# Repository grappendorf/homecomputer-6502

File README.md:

HomeComputer 6502
=================

This is my attempt to build a simple, mobile microcomputer system with an 8-bit MOS 6502 CPU that was used in many popular
home computers of the 1970s and 1980s like the Commodore 64 or the Apple II.

The idea was to design a computer like the C64, almost only using parts that were available when this computer was
manufactured.

The hardware is designed with [Eagle](http://www.cadsoft.de/eagle-pcb-design-software/).

The software is written in 6502 assembler and C, with the help of the [CC65 compiler/assembler](http://cc65.github.io/cc65/).

The case is designed with [Autodesk 123D Design](http://www.123dapp.com/design).

Documentation of this project can be found on my website: http://www.grappendorf.net/projects/6502-home-computer

This repositiory contains the following files:

* eagle - Eagle schematic and board files
* schematics - PDF schematics
* case - 123D/STL design files for the case
* firmware - Minimal BASIC interpreter written with CC65,  different versions of the firmware during the development process
* terminal -  Small ruby script for loading/saving of BASIC programs, example BASIC programs

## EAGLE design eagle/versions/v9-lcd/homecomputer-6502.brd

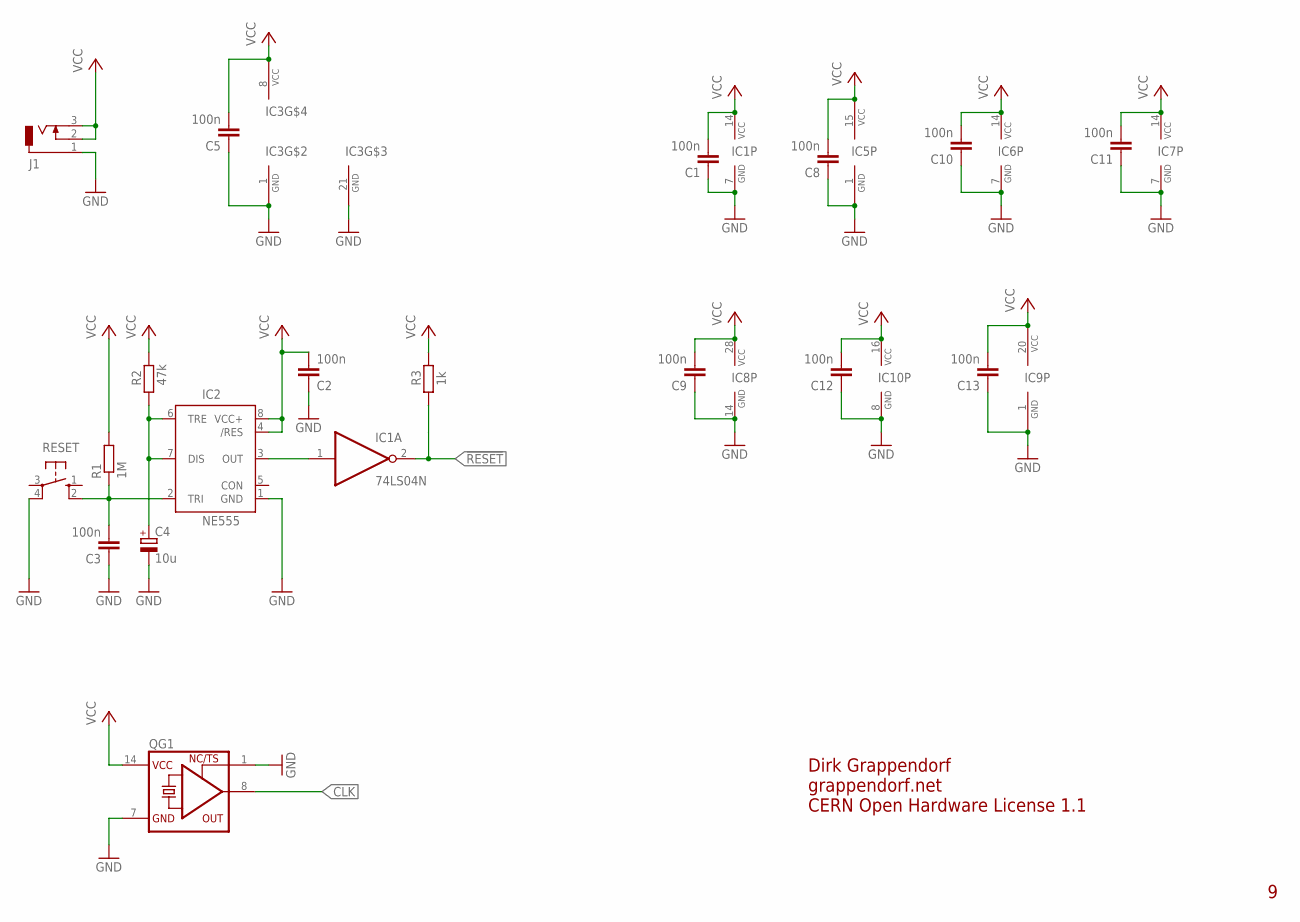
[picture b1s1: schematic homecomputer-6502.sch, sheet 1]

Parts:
C1, C2, C3, C5, C8, C9, C10, C11, C12, C13: 100n; C025-024X044
C4: 10u; E2,5-6E
IC1: 74LS04N; DIL14
IC2: NE555; DIL-08
IC3: 6502; DIP40
IC5: 6551; DIP28
IC6: 74LS00N; DIL14
IC7: 74LS30N; DIL14
IC8: 61256; DIL28-3
IC9: 6522; DIP40
IC10: 74LS137N; DIL16
J1: DCJ0303
QG1: XO-14; DIL14S
R1: 1M; 0204/5
R2: 47k; 0204/5
R3: 1k; 0204/5
RESET: 10-XX; B3F-10XX

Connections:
!RESET: IC1.2 (O), R3.1; also elsewhere on the board
CLK: QG1.8 (OUT); also elsewhere on the board
GND: C1.1, C2.1, C3.1, C4.-, C5.1, C8.1, C9.1, C10.1, C11.1, C12.1, C13.1, IC1.7 (GND), IC2.1 (GND), IC3.1 (GND), IC3.21 (GND), IC5.1 (GND), IC6.7 (GND), IC7.7 (GND), IC8.14 (GND), IC9.1 (GND), IC10.8 (GND), J1.1, QG1.1 (TS), QG1.7 (GND), RESET.4 (P1); also elsewhere on the board
unnamed: C4.+, IC2.6 (TRE), IC2.7 (DIS), R2.1
unnamed: IC1.1 (I), IC2.3 (OUT)
unnamed: C3.2, IC2.2 (TRI), R1.1, RESET.2 (S1)
VCC: C1.2, C2.2, C5.2, C8.2, C9.2, C10.2, C11.2, C12.2, C13.2, IC1.14 (VCC), IC2.4 (/RES), IC2.8 (VCC+), IC3.8 (VCC), IC5.15 (VCC), IC6.14 (VCC), IC7.14 (VCC), IC8.28 (VCC), IC9.20 (VCC), IC10.16 (VCC), J1.2, J1.3, QG1.14 (VCC), R1.2, R2.2, R3.2; also elsewhere on the board

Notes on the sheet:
Dirk Grappendorf
grappendorf.net
CERN Open Hardware License 1.1

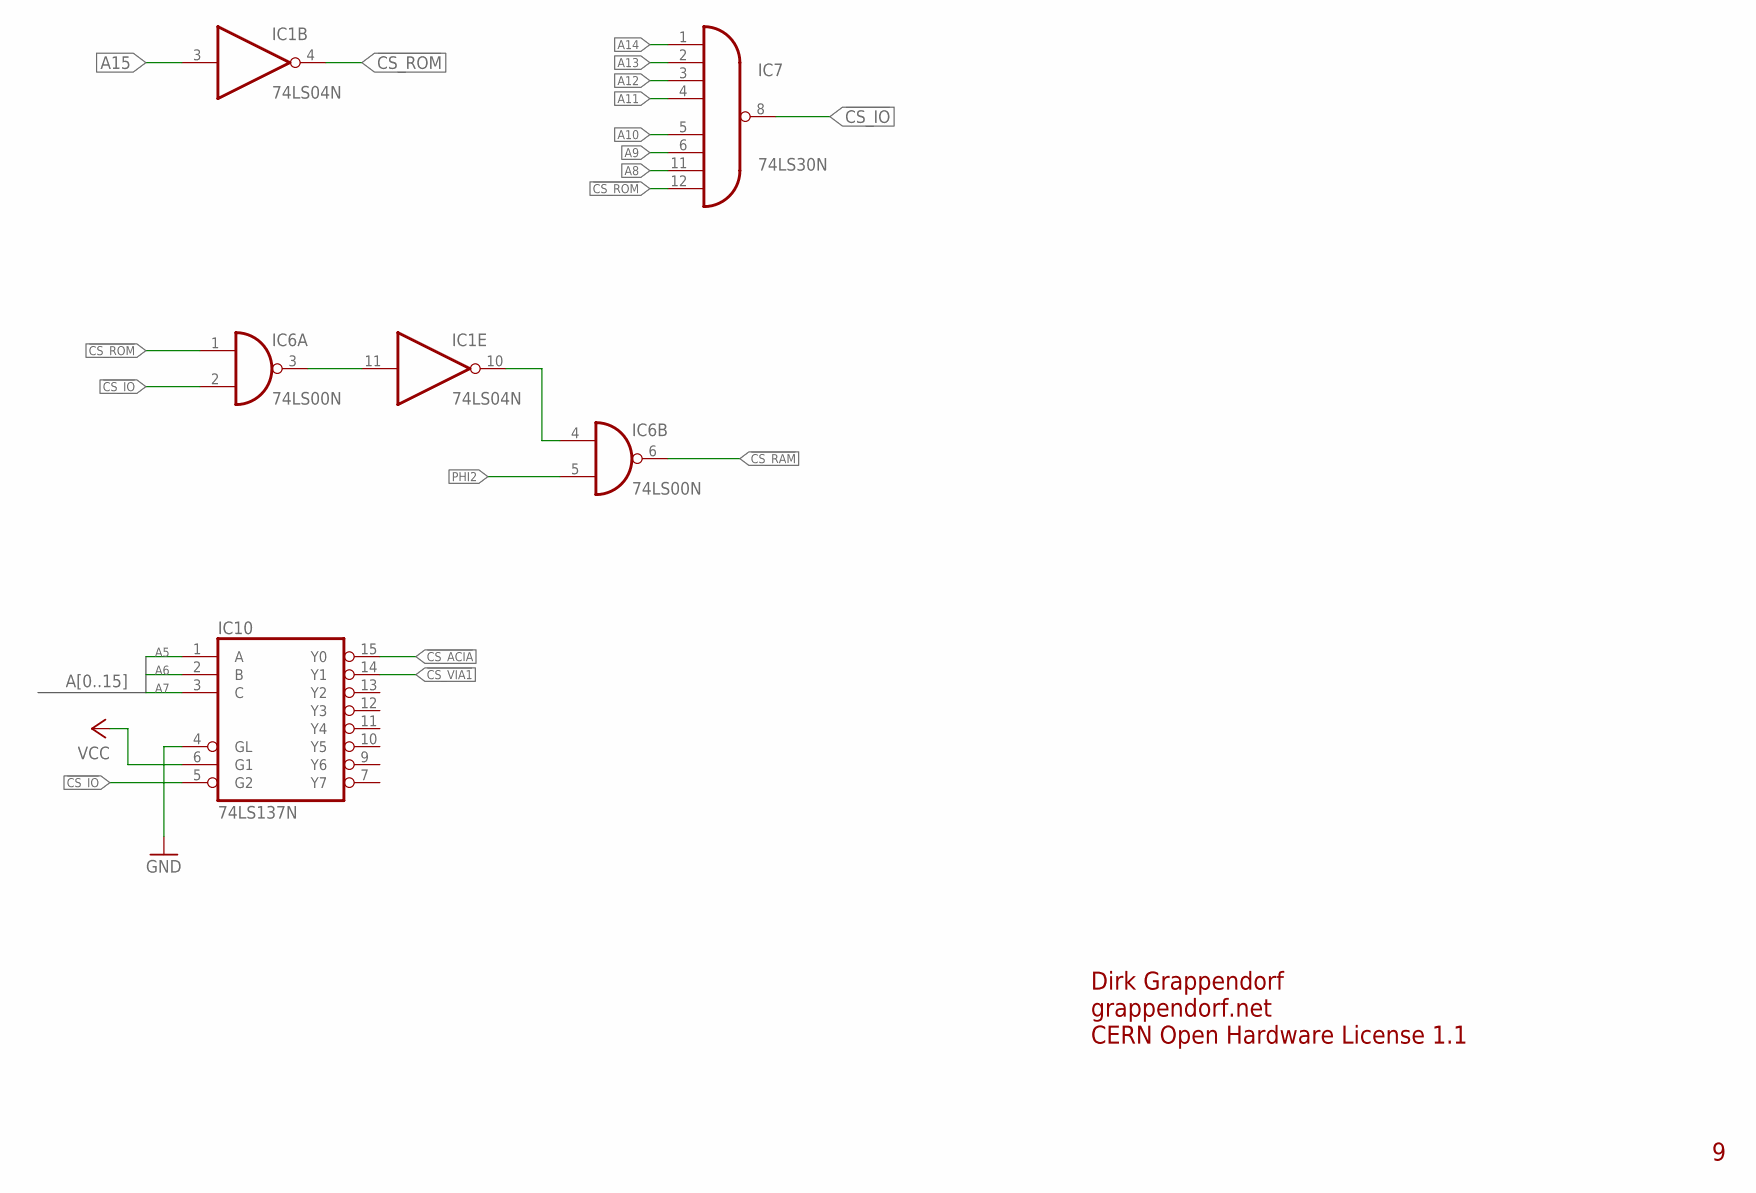
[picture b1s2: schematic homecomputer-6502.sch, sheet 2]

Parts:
IC1: 74LS04N; DIL14
IC6: 74LS00N; DIL14
IC7: 74LS30N; DIL14
IC10: 74LS137N; DIL16

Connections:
!CS_ACIA: IC10.15 (Y0); also elsewhere on the board
!CS_IO: IC6.2 (I1), IC7.8 (O), IC10.5 (G2)
!CS_RAM: IC6.6 (O); also elsewhere on the board
!CS_ROM: IC1.4 (O), IC6.1 (I0), IC7.12 (I7); also elsewhere on the board
!CS_VIA1: IC10.14 (Y1); also elsewhere on the board
A5: IC10.1 (A); also elsewhere on the board
A6: IC10.2 (B); also elsewhere on the board
A7: IC10.3 (C); also elsewhere on the board
A8: IC7.11 (I6); also elsewhere on the board
A9: IC7.6 (I5); also elsewhere on the board
A10: IC7.5 (I4); also elsewhere on the board
A11: IC7.4 (I3); also elsewhere on the board
A12: IC7.3 (I2); also elsewhere on the board
A13: IC7.2 (I1); also elsewhere on the board
A14: IC7.1 (I0); also elsewhere on the board
A15: IC1.3 (I); also elsewhere on the board
GND: IC10.4 (GL); also elsewhere on the board
unnamed: IC1.11 (I), IC6.3 (O)
unnamed: IC1.10 (O), IC6.4 (I0)
PHI2: IC6.5 (I1); also elsewhere on the board
VCC: IC10.6 (G1); also elsewhere on the board

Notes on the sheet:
Dirk Grappendorf
grappendorf.net
CERN Open Hardware License 1.1

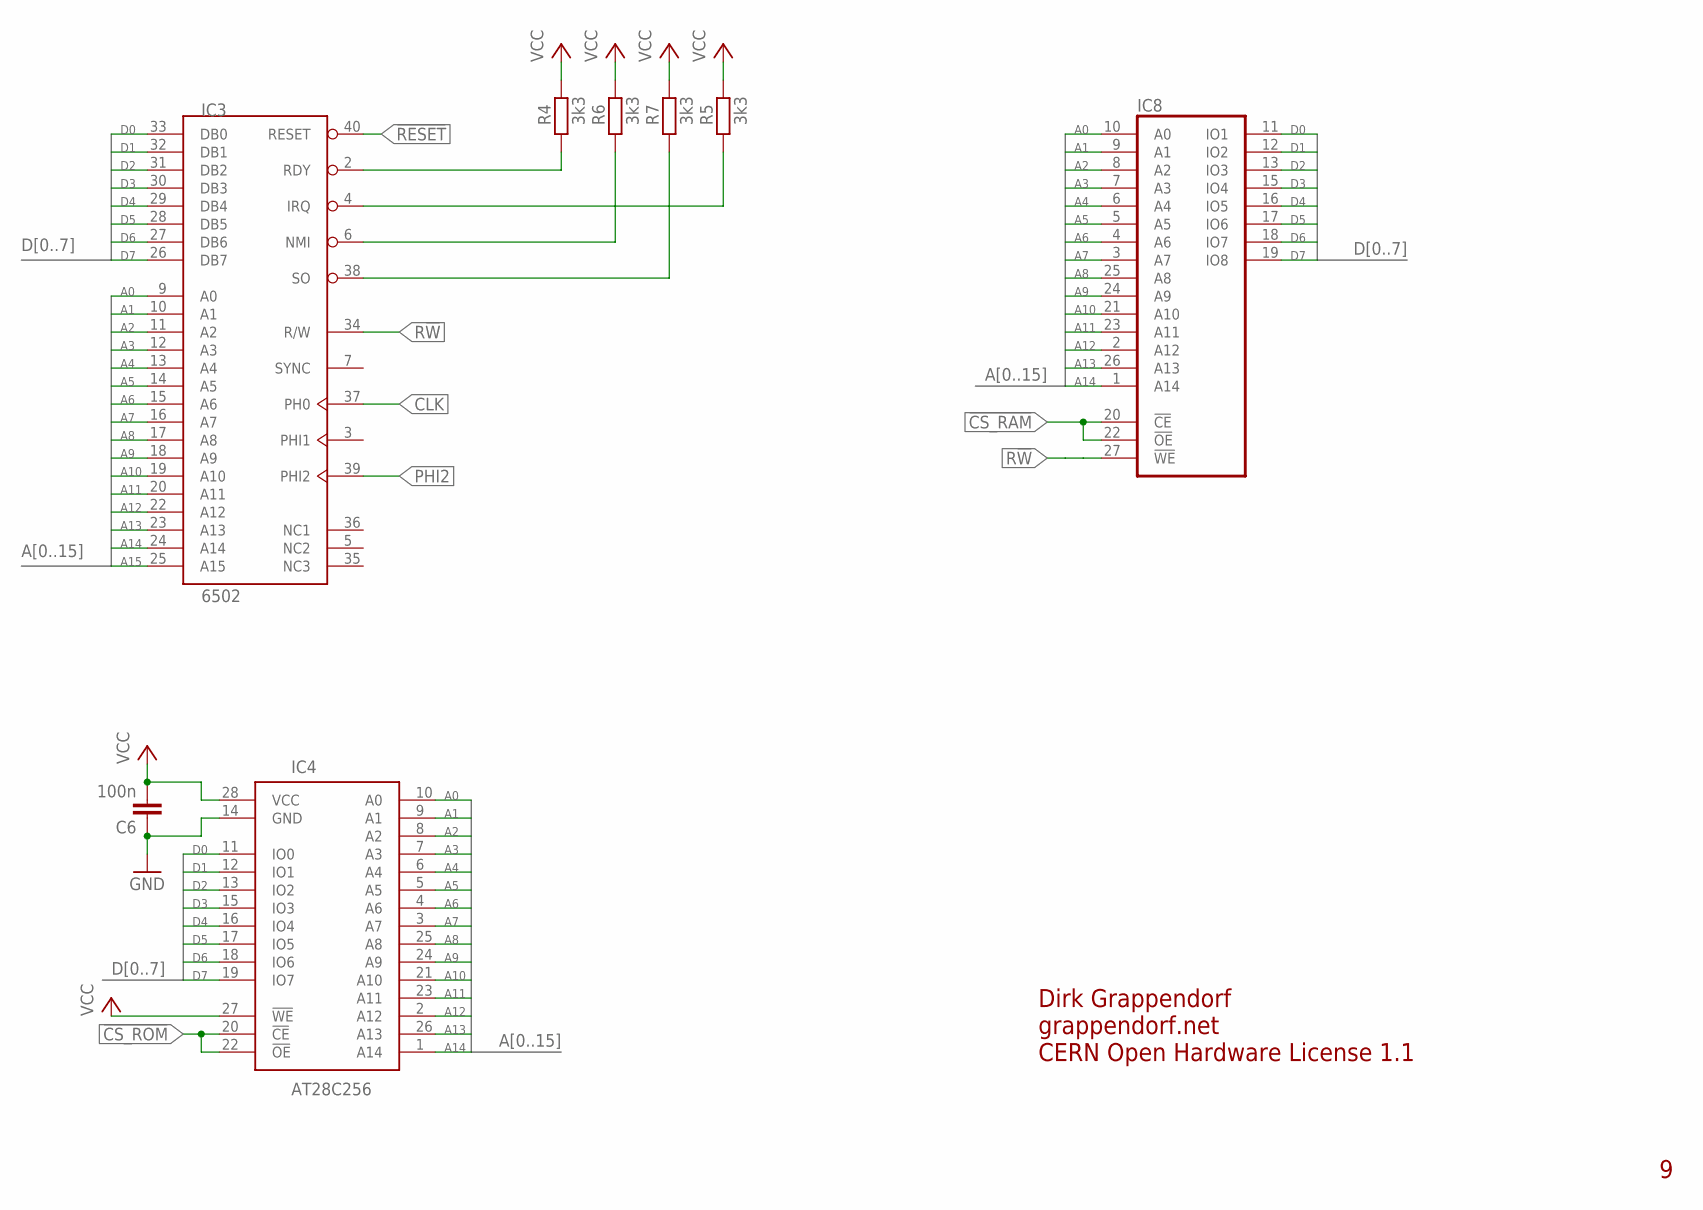
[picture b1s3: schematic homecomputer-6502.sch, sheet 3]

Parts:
C6: 100n; C025-024X044
IC3: 6502; DIP40
IC4: AT28C256; DIL28-6
IC8: 61256; DIL28-3
R4, R5, R6, R7: 3k3; 0204/5

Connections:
!CS_RAM: IC8.20 (!CE), IC8.22 (!OE); also elsewhere on the board
!CS_ROM: IC4.20 (!CE), IC4.22 (!OE); also elsewhere on the board
!IRQ: IC3.4 (IRQ), R5.1
!RESET: IC3.40 (RESET); also elsewhere on the board
A0: IC3.9 (A0), IC4.10 (A0), IC8.10 (A0); also elsewhere on the board
A1: IC3.10 (A1), IC4.9 (A1), IC8.9 (A1); also elsewhere on the board
A2: IC3.11 (A2), IC4.8 (A2), IC8.8 (A2); also elsewhere on the board
A3: IC3.12 (A3), IC4.7 (A3), IC8.7 (A3); also elsewhere on the board
A4: IC3.13 (A4), IC4.6 (A4), IC8.6 (A4)
A5: IC3.14 (A5), IC4.5 (A5), IC8.5 (A5); also elsewhere on the board
A6: IC3.15 (A6), IC4.4 (A6), IC8.4 (A6); also elsewhere on the board
A7: IC3.16 (A7), IC4.3 (A7), IC8.3 (A7); also elsewhere on the board
A8: IC3.17 (A8), IC4.25 (A8), IC8.25 (A8); also elsewhere on the board
A9: IC3.18 (A9), IC4.24 (A9), IC8.24 (A9); also elsewhere on the board
A10: IC3.19 (A10), IC4.21 (A10), IC8.21 (A10); also elsewhere on the board
A11: IC3.20 (A11), IC4.23 (A11), IC8.23 (A11); also elsewhere on the board
A12: IC3.22 (A12), IC4.2 (A12), IC8.2 (A12); also elsewhere on the board
A13: IC3.23 (A13), IC4.26 (A13), IC8.26 (A13); also elsewhere on the board
A14: IC3.24 (A14), IC4.1 (A14), IC8.1 (A14); also elsewhere on the board
A15: IC3.25 (A15); also elsewhere on the board
CLK: IC3.37 (PH0); also elsewhere on the board
D0: IC3.33 (DB0), IC4.11 (IO0), IC8.11 (IO1); also elsewhere on the board
D1: IC3.32 (DB1), IC4.12 (IO1), IC8.12 (IO2); also elsewhere on the board
D2: IC3.31 (DB2), IC4.13 (IO2), IC8.13 (IO3); also elsewhere on the board
D3: IC3.30 (DB3), IC4.15 (IO3), IC8.15 (IO4); also elsewhere on the board
D4: IC3.29 (DB4), IC4.16 (IO4), IC8.16 (IO5); also elsewhere on the board
D5: IC3.28 (DB5), IC4.17 (IO5), IC8.17 (IO6); also elsewhere on the board
D6: IC3.27 (DB6), IC4.18 (IO6), IC8.18 (IO7); also elsewhere on the board
D7: IC3.26 (DB7), IC4.19 (IO7), IC8.19 (IO8); also elsewhere on the board
GND: C6.1, IC4.14 (GND); also elsewhere on the board
unnamed: IC3.2 (RDY), R4.1
unnamed: IC3.6 (NMI), R6.1
unnamed: IC3.38 (SO), R7.1
PHI2: IC3.39 (PHI2); also elsewhere on the board
R!W: IC3.34 (R/W), IC8.27 (!WE); also elsewhere on the board
VCC: C6.2, IC4.27 (!WE), IC4.28 (VCC), R4.2, R5.2, R6.2, R7.2; also elsewhere on the board

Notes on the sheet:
Dirk Grappendorf
grappendorf.net
CERN Open Hardware License 1.1

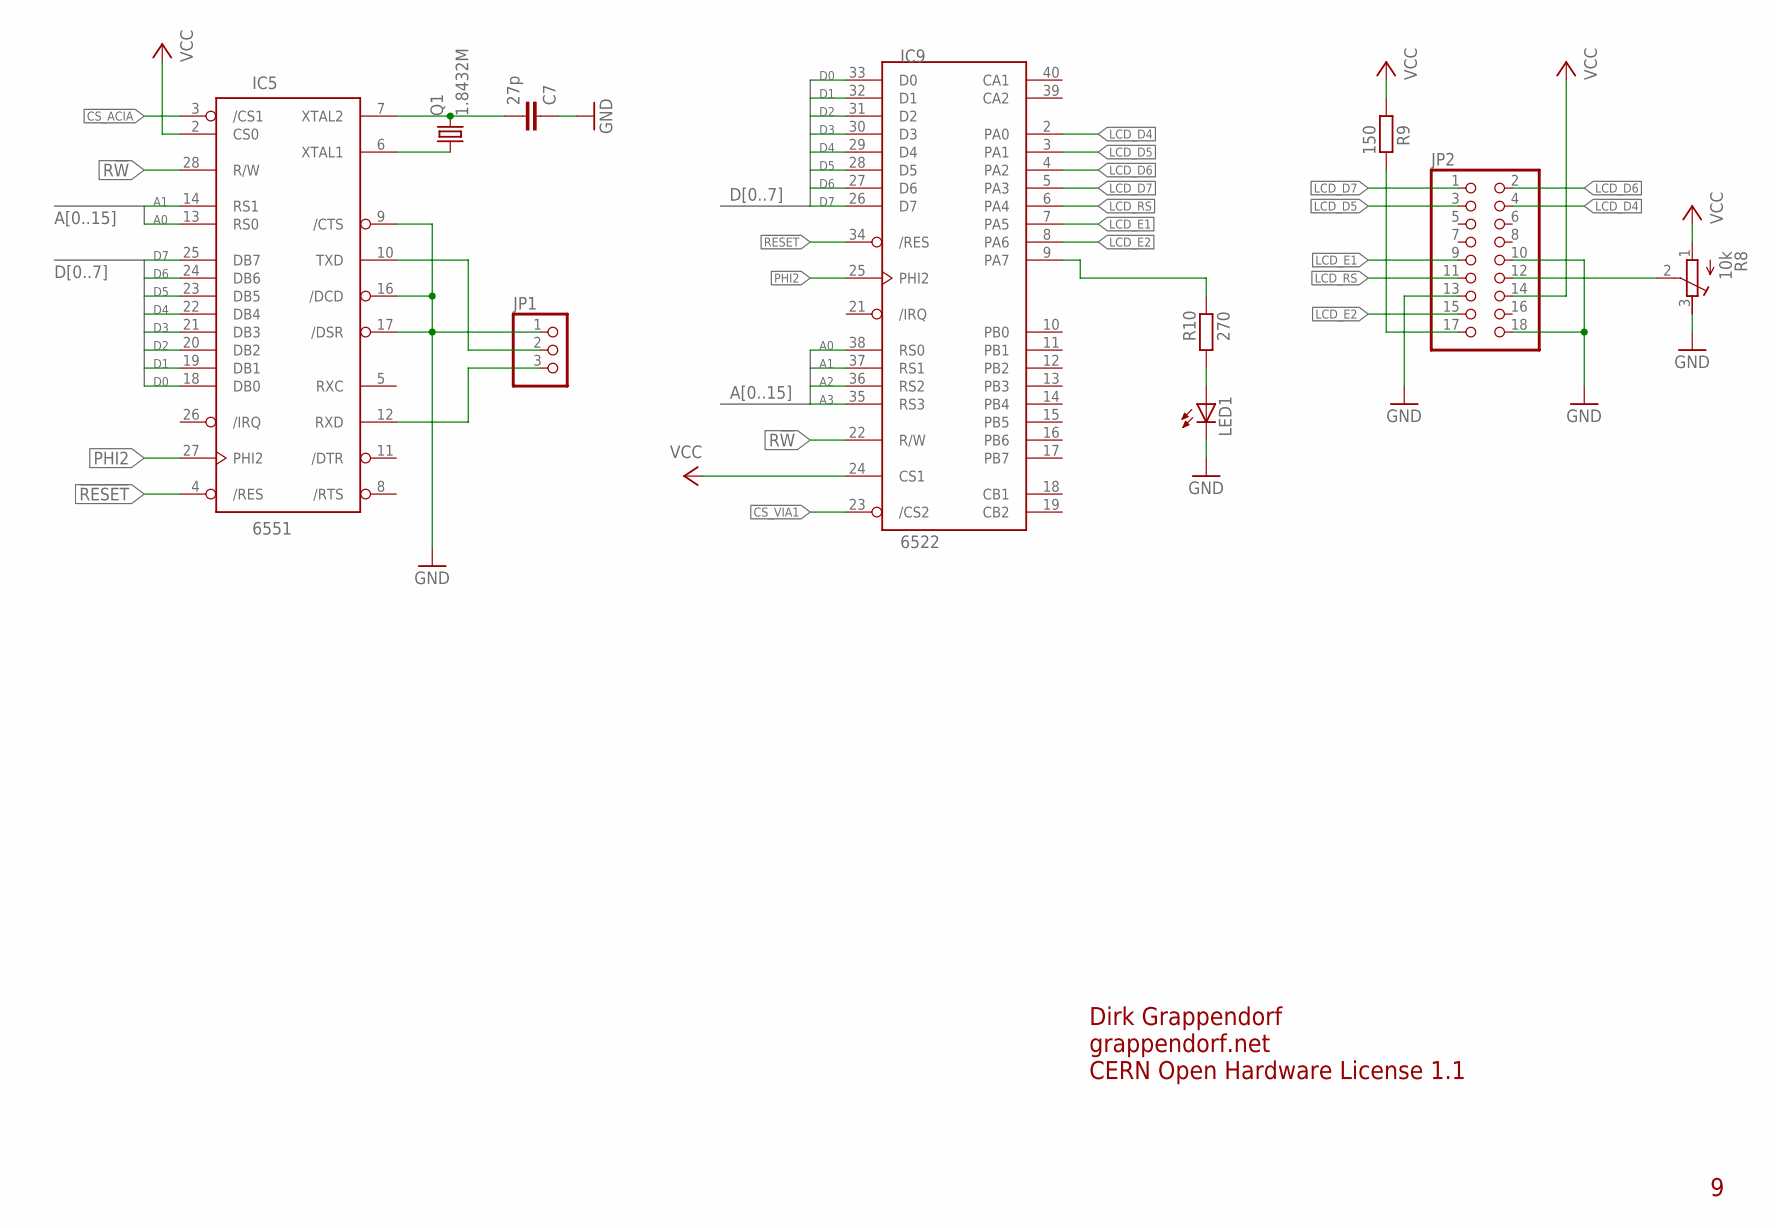
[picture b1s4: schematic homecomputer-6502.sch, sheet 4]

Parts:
C7: 27p; C025-024X044
IC5: 6551; DIP28
IC9: 6522; DIP40
JP1: PINHD-1X3_2.54; 1X03
JP2: PINHD-2X9_2.54; 2X09
LED1: LED3MM
Q1: 1.8432M; HC49U-V
R8: 10k; RTRIM3339P
R9: 150; 0204/5
R10: 270; 0204/5

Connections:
!CS_ACIA: IC5.3 (/CS1); also elsewhere on the board
!CS_VIA1: IC9.23 (/CS2); also elsewhere on the board
!RESET: IC5.4 (/RES), IC9.34 (/RES); also elsewhere on the board
A0: IC5.13 (RS0), IC9.38 (RS0); also elsewhere on the board
A1: IC5.14 (RS1), IC9.37 (RS1); also elsewhere on the board
A2: IC9.36 (RS2); also elsewhere on the board
A3: IC9.35 (RS3); also elsewhere on the board
D0: IC5.18 (DB0), IC9.33 (D0); also elsewhere on the board
D1: IC5.19 (DB1), IC9.32 (D1); also elsewhere on the board
D2: IC5.20 (DB2), IC9.31 (D2); also elsewhere on the board
D3: IC5.21 (DB3), IC9.30 (D3); also elsewhere on the board
D4: IC5.22 (DB4), IC9.29 (D4); also elsewhere on the board
D5: IC5.23 (DB5), IC9.28 (D5); also elsewhere on the board
D6: IC5.24 (DB6), IC9.27 (D6); also elsewhere on the board
D7: IC5.25 (DB7), IC9.26 (D7); also elsewhere on the board
GND: C7.1, IC5.9 (/CTS), IC5.16 (/DCD), IC5.17 (/DSR), JP1.1, JP2.10, JP2.13, JP2.18, LED1.K (C), R8.3 (E); also elsewhere on the board
LCD_D4: IC9.2 (PA0), JP2.4
LCD_D5: IC9.3 (PA1), JP2.3
LCD_D6: IC9.4 (PA2), JP2.2
LCD_D7: IC9.5 (PA3), JP2.1
LCD_E1: IC9.7 (PA5), JP2.9
LCD_E2: IC9.8 (PA6), JP2.15
LCD_RS: IC9.6 (PA4), JP2.11
unnamed: C7.2, IC5.7 (XTAL2), Q1.2
unnamed: IC5.6 (XTAL1), Q1.1
unnamed: IC5.10 (TXD), JP1.2
unnamed: IC9.9 (PA7), R10.2
unnamed: IC5.12 (RXD), JP1.3
unnamed: JP2.12, R8.2 (S)
unnamed: JP2.17, R9.2
unnamed: LED1.A, R10.1
PHI2: IC5.27 (PHI2), IC9.25 (PHI2); also elsewhere on the board
R!W: IC5.28 (R/W), IC9.22 (R/W); also elsewhere on the board
VCC: IC5.2 (CS0), IC9.24 (CS1), JP2.14, R8.1 (A), R9.1; also elsewhere on the board

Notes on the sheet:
Dirk Grappendorf
grappendorf.net
CERN Open Hardware License 1.1

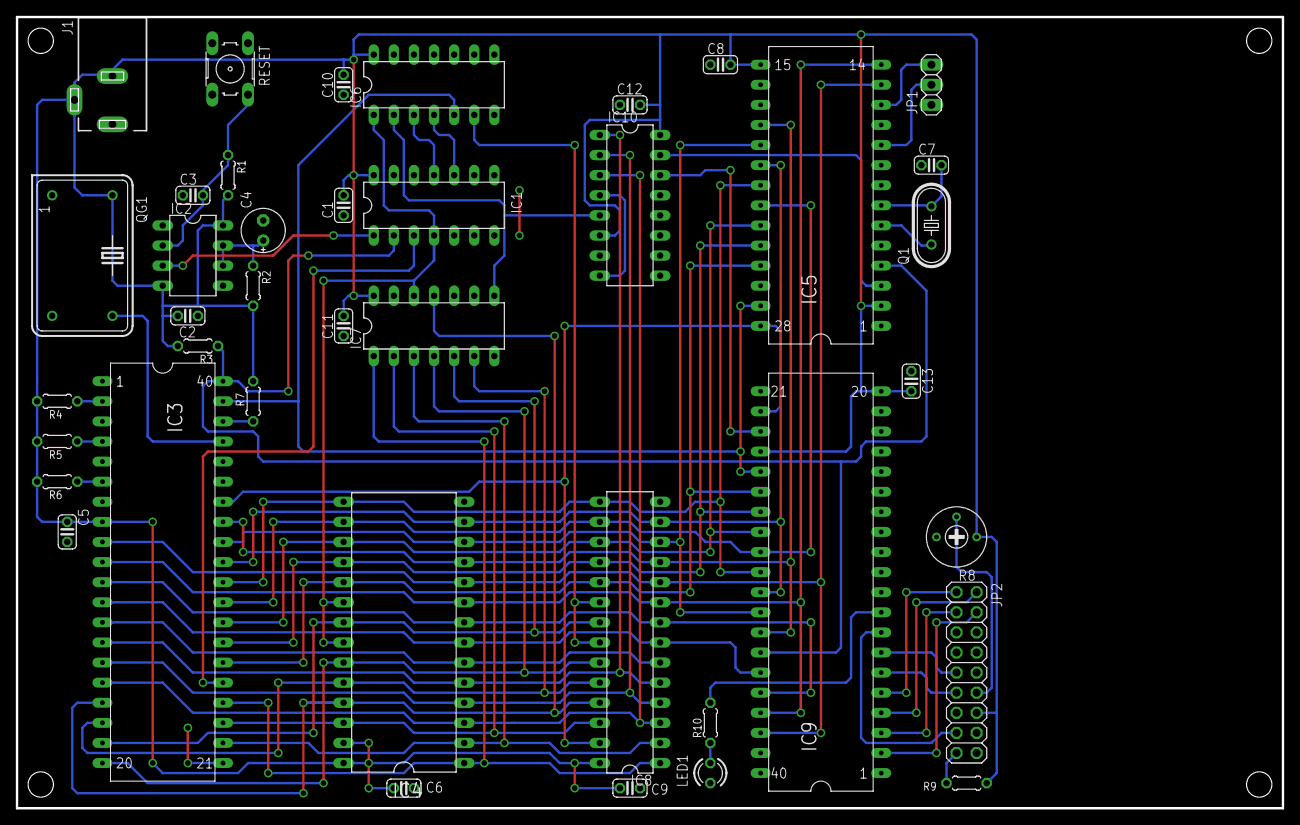
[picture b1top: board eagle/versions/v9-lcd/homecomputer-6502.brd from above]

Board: 3 copper layers, 160.0 x 100.0 mm, 40 parts (0 on the bottom side), 59 nets.

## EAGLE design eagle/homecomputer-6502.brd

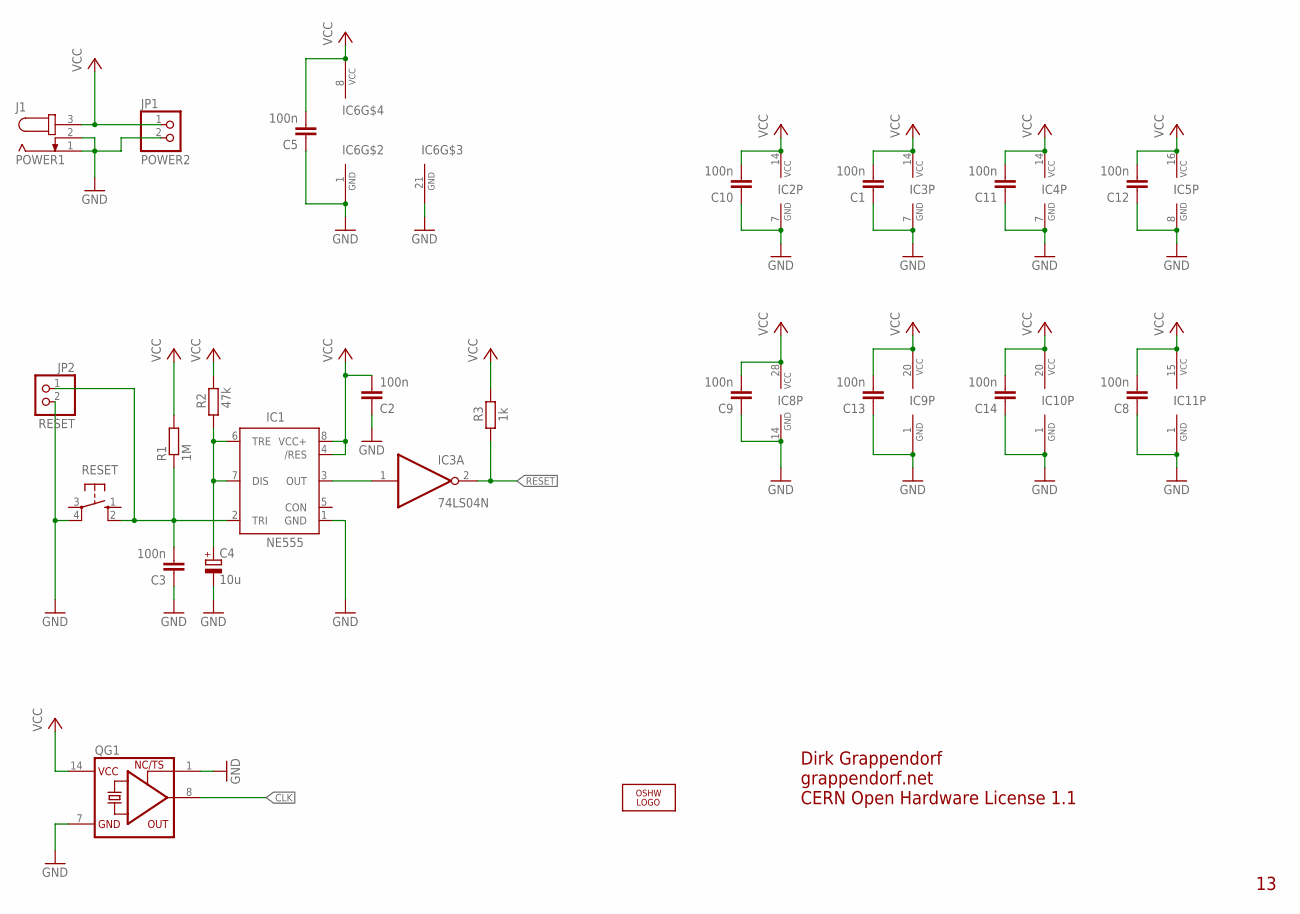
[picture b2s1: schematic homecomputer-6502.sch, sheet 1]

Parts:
C1, C2, C3, C5, C8, C9, C10, C11, C12, C13, C14: 100n; C025-024X044
C4: 10u; E2,5-6E
IC1: NE555; DIL-08
IC2: 74LS00N; DIL14
IC3: 74LS04N; DIL14
IC4: 74LS30N; DIL14
IC5: 74LS137N; DIL16
IC6: 6502; DIP40
IC8: 61256; DIL28-3
IC9, IC10: 6522; DIP40
IC11: 6551; DIP28
J1: POWER1; SPC4078
JP1: POWER2; 1X02
JP2: RESET; 1X02
LOGO1: OSHW_LOGO_8MILX0350-NT; OSHW_8X350_NOTEXT
QG1: XO-14; DIL14S
R1: 1M; 0204/7
R2: 47k; 0204/7
R3: 1k; 0204/7
RESET: 10-XX; B3F-10XX

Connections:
!RESET: IC3.2 (O), R3.1; also elsewhere on the board
CLK: QG1.8 (OUT); also elsewhere on the board
GND: C1.1, C2.1, C3.1, C4.-, C5.1, C8.1, C9.1, C10.1, C11.1, C12.1, C13.1, C14.1, IC1.1 (GND), IC2.7 (GND), IC3.7 (GND), IC4.7 (GND), IC5.8 (GND), IC6.1 (GND), IC6.21 (GND), IC8.14 (GND), IC9.1 (GND), IC10.1 (GND), IC11.1 (GND), J1.1, J1.2, JP1.2, JP2.2, QG1.1 (TS), QG1.7 (GND), RESET.4 (P1); also elsewhere on the board
unnamed: C4.+, IC1.6 (TRE), IC1.7 (DIS), R2.1
unnamed: IC1.3 (OUT), IC3.1 (I)
unnamed: C3.2, IC1.2 (TRI), JP2.1, R1.1, RESET.2 (S1)
VCC: C1.2, C2.2, C5.2, C8.2, C9.2, C10.2, C11.2, C12.2, C13.2, C14.2, IC1.4 (/RES), IC1.8 (VCC+), IC2.14 (VCC), IC3.14 (VCC), IC4.14 (VCC), IC5.16 (VCC), IC6.8 (VCC), IC8.28 (VCC), IC9.20 (VCC), IC10.20 (VCC), IC11.15 (VCC), J1.3, JP1.1, QG1.14 (VCC), R1.2, R2.2, R3.2; also elsewhere on the board

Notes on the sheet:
Dirk Grappendorf
grappendorf.net
CERN Open Hardware License 1.1

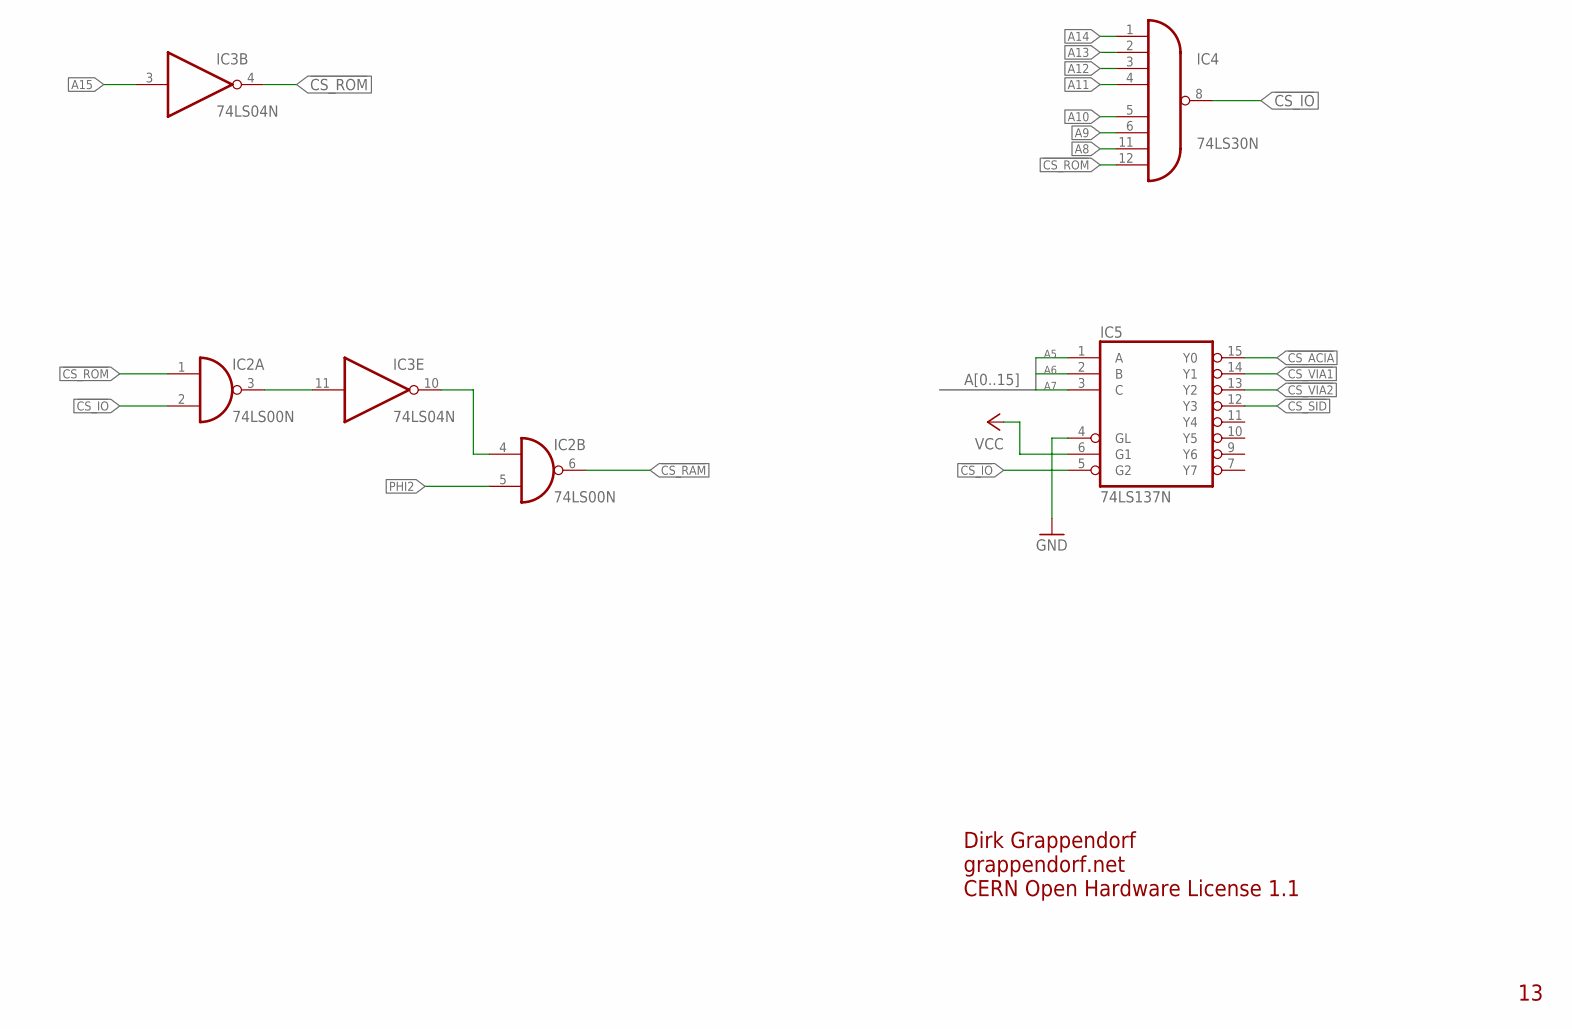
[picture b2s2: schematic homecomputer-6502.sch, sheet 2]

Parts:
IC2: 74LS00N; DIL14
IC3: 74LS04N; DIL14
IC4: 74LS30N; DIL14
IC5: 74LS137N; DIL16

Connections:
!CS_ACIA: IC5.15 (Y0); also elsewhere on the board
!CS_IO: IC2.2 (I1), IC4.8 (O), IC5.5 (G2)
!CS_RAM: IC2.6 (O); also elsewhere on the board
!CS_ROM: IC2.1 (I0), IC3.4 (O), IC4.12 (I7); also elsewhere on the board
!CS_SID: IC5.12 (Y3); also elsewhere on the board
!CS_VIA1: IC5.14 (Y1); also elsewhere on the board
!CS_VIA2: IC5.13 (Y2); also elsewhere on the board
A5: IC5.1 (A); also elsewhere on the board
A6: IC5.2 (B); also elsewhere on the board
A7: IC5.3 (C); also elsewhere on the board
A8: IC4.11 (I6); also elsewhere on the board
A9: IC4.6 (I5); also elsewhere on the board
A10: IC4.5 (I4); also elsewhere on the board
A11: IC4.4 (I3); also elsewhere on the board
A12: IC4.3 (I2); also elsewhere on the board
A13: IC4.2 (I1); also elsewhere on the board
A14: IC4.1 (I0); also elsewhere on the board
A15: IC3.3 (I); also elsewhere on the board
GND: IC5.4 (GL); also elsewhere on the board
unnamed: IC2.3 (O), IC3.11 (I)
unnamed: IC2.4 (I0), IC3.10 (O)
PHI2: IC2.5 (I1); also elsewhere on the board
VCC: IC5.6 (G1); also elsewhere on the board

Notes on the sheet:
Dirk Grappendorf
grappendorf.net
CERN Open Hardware License 1.1

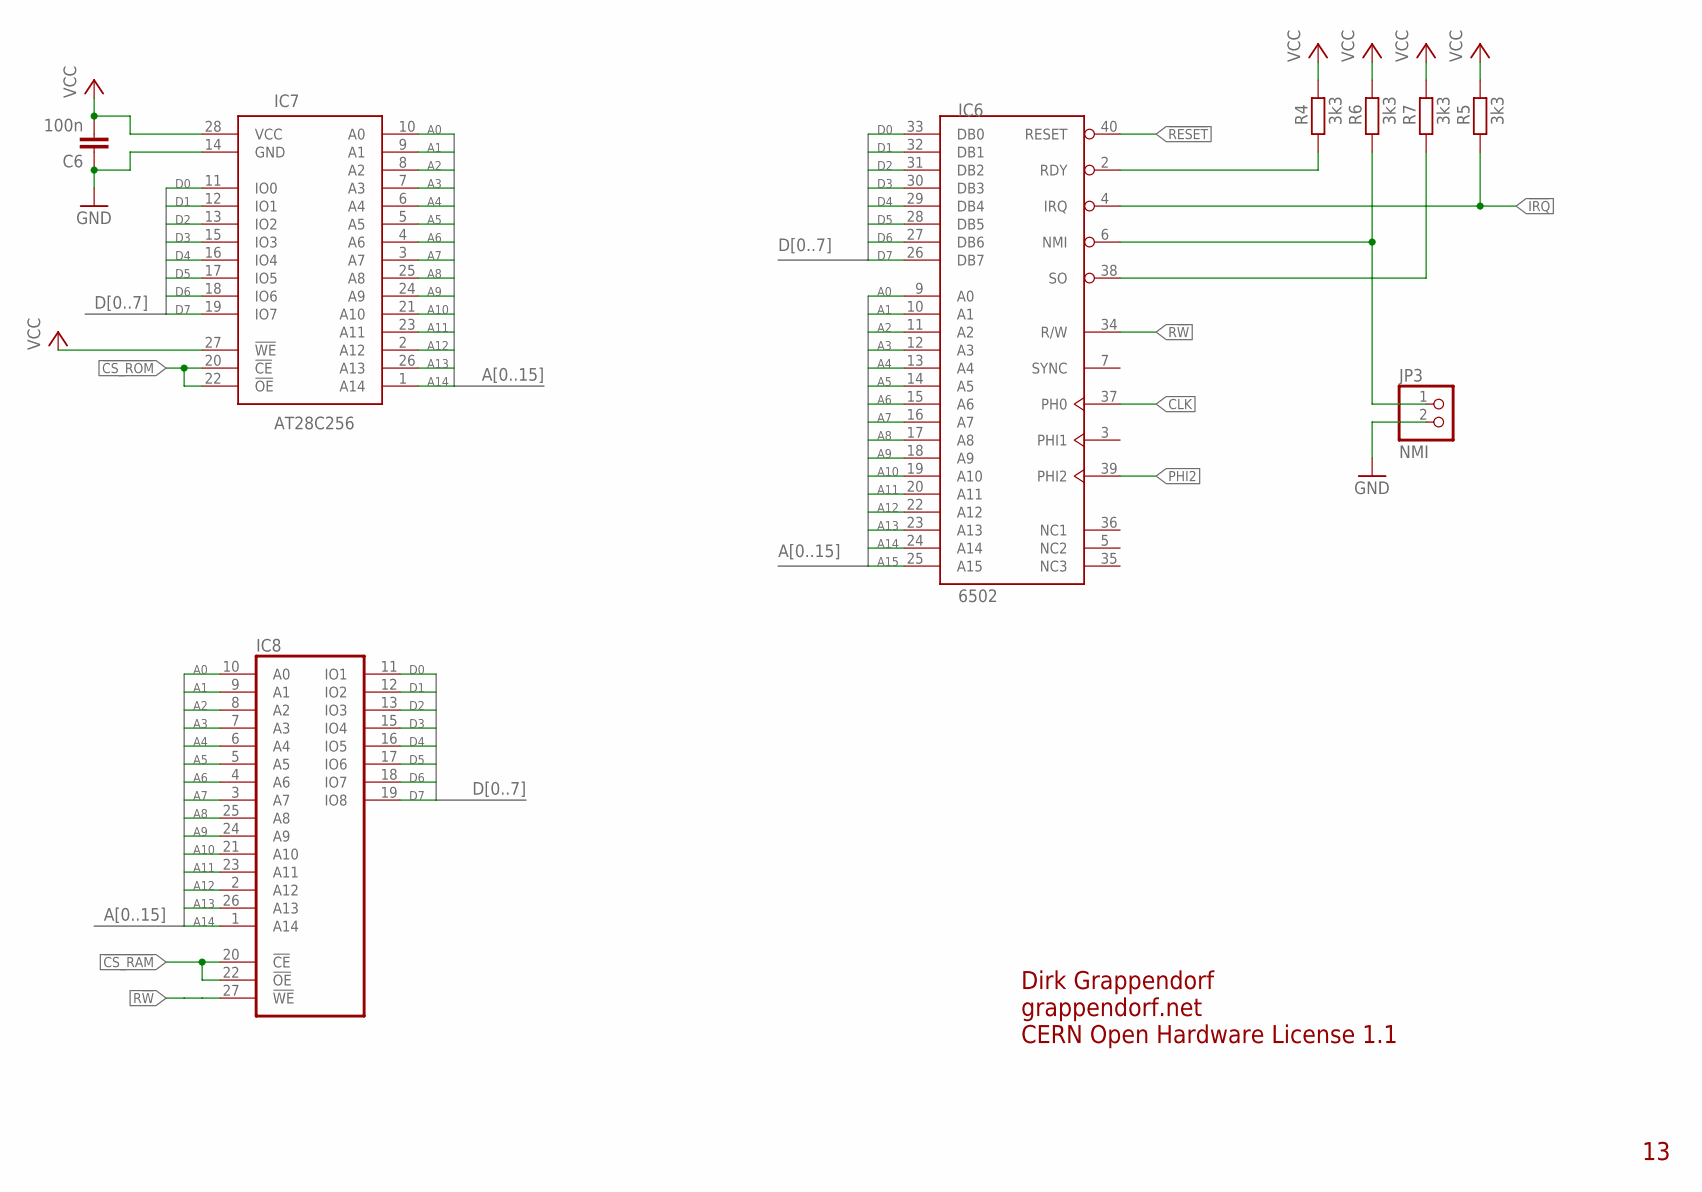
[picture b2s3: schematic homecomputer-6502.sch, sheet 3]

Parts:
C6: 100n; C025-024X044
IC6: 6502; DIP40
IC7: AT28C256; DIL28-6
IC8: 61256; DIL28-3
JP3: NMI; 1X02
R4, R5, R6, R7: 3k3; 0204/7

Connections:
!CS_RAM: IC8.20 (!CE), IC8.22 (!OE); also elsewhere on the board
!CS_ROM: IC7.20 (!CE), IC7.22 (!OE); also elsewhere on the board
!IRQ: IC6.4 (IRQ), R5.1; also elsewhere on the board
!RESET: IC6.40 (RESET); also elsewhere on the board
A0: IC6.9 (A0), IC7.10 (A0), IC8.10 (A0); also elsewhere on the board
A1: IC6.10 (A1), IC7.9 (A1), IC8.9 (A1); also elsewhere on the board
A2: IC6.11 (A2), IC7.8 (A2), IC8.8 (A2); also elsewhere on the board
A3: IC6.12 (A3), IC7.7 (A3), IC8.7 (A3); also elsewhere on the board
A4: IC6.13 (A4), IC7.6 (A4), IC8.6 (A4); also elsewhere on the board
A5: IC6.14 (A5), IC7.5 (A5), IC8.5 (A5); also elsewhere on the board
A6: IC6.15 (A6), IC7.4 (A6), IC8.4 (A6); also elsewhere on the board
A7: IC6.16 (A7), IC7.3 (A7), IC8.3 (A7); also elsewhere on the board
A8: IC6.17 (A8), IC7.25 (A8), IC8.25 (A8); also elsewhere on the board
A9: IC6.18 (A9), IC7.24 (A9), IC8.24 (A9); also elsewhere on the board
A10: IC6.19 (A10), IC7.21 (A10), IC8.21 (A10); also elsewhere on the board
A11: IC6.20 (A11), IC7.23 (A11), IC8.23 (A11); also elsewhere on the board
A12: IC6.22 (A12), IC7.2 (A12), IC8.2 (A12); also elsewhere on the board
A13: IC6.23 (A13), IC7.26 (A13), IC8.26 (A13); also elsewhere on the board
A14: IC6.24 (A14), IC7.1 (A14), IC8.1 (A14); also elsewhere on the board
A15: IC6.25 (A15); also elsewhere on the board
CLK: IC6.37 (PH0); also elsewhere on the board
D0: IC6.33 (DB0), IC7.11 (IO0), IC8.11 (IO1); also elsewhere on the board
D1: IC6.32 (DB1), IC7.12 (IO1), IC8.12 (IO2); also elsewhere on the board
D2: IC6.31 (DB2), IC7.13 (IO2), IC8.13 (IO3); also elsewhere on the board
D3: IC6.30 (DB3), IC7.15 (IO3), IC8.15 (IO4); also elsewhere on the board
D4: IC6.29 (DB4), IC7.16 (IO4), IC8.16 (IO5); also elsewhere on the board
D5: IC6.28 (DB5), IC7.17 (IO5), IC8.17 (IO6); also elsewhere on the board
D6: IC6.27 (DB6), IC7.18 (IO6), IC8.18 (IO7); also elsewhere on the board
D7: IC6.26 (DB7), IC7.19 (IO7), IC8.19 (IO8); also elsewhere on the board
GND: C6.1, IC7.14 (GND), JP3.2; also elsewhere on the board
unnamed: IC6.2 (RDY), R4.1
unnamed: IC6.6 (NMI), JP3.1, R6.1
unnamed: IC6.38 (SO), R7.1
PHI2: IC6.39 (PHI2); also elsewhere on the board
R!W: IC6.34 (R/W), IC8.27 (!WE); also elsewhere on the board
VCC: C6.2, IC7.27 (!WE), IC7.28 (VCC), R4.2, R5.2, R6.2, R7.2; also elsewhere on the board

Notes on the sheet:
Dirk Grappendorf
grappendorf.net
CERN Open Hardware License 1.1
